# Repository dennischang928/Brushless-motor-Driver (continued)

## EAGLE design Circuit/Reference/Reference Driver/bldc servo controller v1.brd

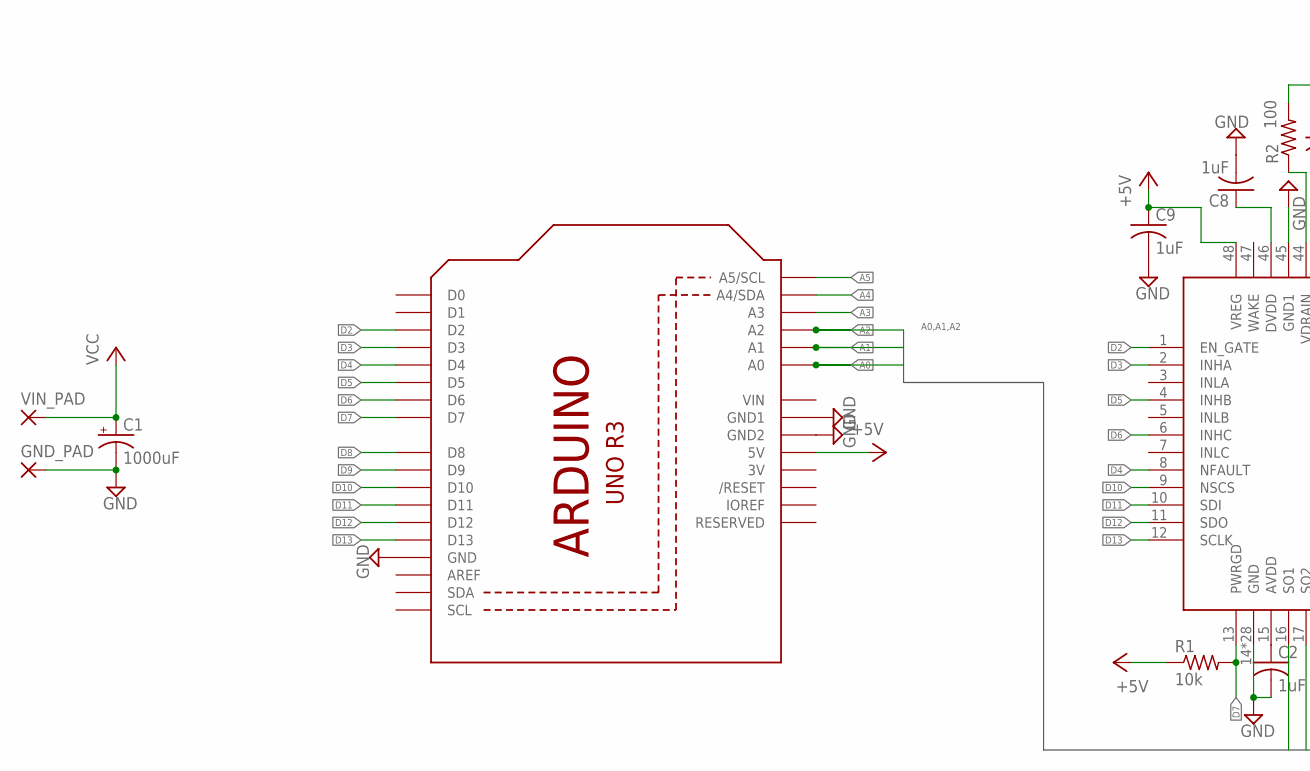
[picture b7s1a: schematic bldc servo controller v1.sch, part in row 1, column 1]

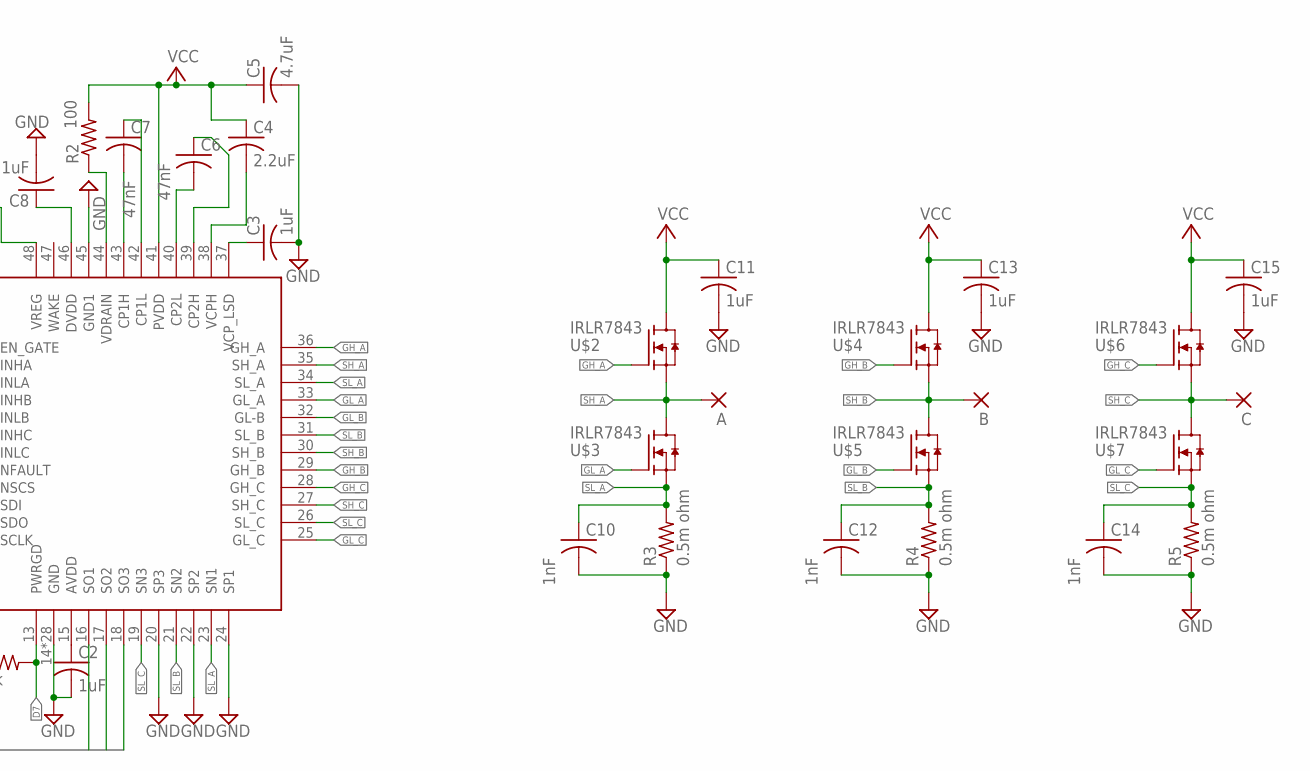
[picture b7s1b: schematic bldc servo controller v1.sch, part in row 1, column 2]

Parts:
A: WIREPAD1,6/0,8; 1,6/0,8
B: WIREPAD1,6/0,8; 1,6/0,8
C: WIREPAD1,6/0,8; 1,6/0,8
C1: 1000uF; E3,5-10
C2, C3, C8, C9, C11, C13, C15: 1uF; C0805
C4: 2.2uF; C0805
C5: 4.7uF; C0805
C6, C7: 47nF; C0805
C10, C12, C14: 1nF; C0805
GND_PAD: WIREPAD1,6/0,8; 1,6/0,8
R1: 10k; M0805
R2: 100; M0805
R3, R4, R5: 0.5m ohm; R2512
U1: ARDUINOR3-BPLACE
U$1: DRV8305; PFB_S-PQFP-G48
U$2, U$3, U$4, U$5, U$6, U$7: IRLR7843; TO252
VIN_PAD: WIREPAD1,6/0,8; 1,6/0,8

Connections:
3V: U1.3V
+5V: C9.1, R1.1, U1.5V, U$1.48 (VREG)
A0: U1.A0, U$1.16 (SO1)
A1: U1.A1, U$1.17 (SO2)
A2: U1.A2, U$1.18 (SO3)
A3: U1.A3
A4: U1.A4 (A4/SDA)
A5: U1.A5 (A5/SCL)
D2: U1.D2, U$1.1 (EN_GATE)
D3: U1.D3, U$1.2 (INHA)
D4: U1.D4, U$1.8 (NFAULT)
D5: U1.D5, U$1.4 (INHB)
D6: U1.D6, U$1.6 (INHC)
D7: R1.2, U1.D7, U$1.13 (PWRGD)
D8: U1.D8
D9: U1.D9
D10: U1.D10, U$1.9 (NSCS)
D11: U1.D11, U$1.10 (SDI)
D12: U1.D12, U$1.11 (SDO)
D13: U1.D13, U$1.12 (SCLK)
GH_A: U$1.36 (GH_A), U$2.1 (G)
GH_B: U$1.29 (GH_B), U$4.1 (G)
GH_C: U$1.28 (GH_C), U$6.1 (G)
GL_A: U$1.33 (GL_A), U$3.1 (G)
GL_B: U$1.32 (GL-B), U$5.1 (G)
GL_C: U$1.25 (GL_C), U$7.1 (G)
GND: C1.-, C2.2, C3.2, C5.2, C8.2, C9.2, C10.2, C11.2, C12.2, C13.2, C14.2, C15.2, GND_PAD.1, R3.1, R4.1, R5.1, U1.GND, U1.GND1, U1.GND2, U$1.14 (GND), U$1.20 (SP3), U$1.22 (SP2), U$1.24 (SP1), U$1.45 (GND1), U$1.P$1 (GND), U$1.P$2 (GND), U$1.P$3 (GND), U$1.P$4 (GND), U$1.P$5 (GND), U$1.P$6 (GND), U$1.P$7 (GND), U$1.P$8 (GND), U$1.P$9 (GND), U$1.P$10 (GND), U$1.P$11 (GND), U$1.P$12 (GND), U$1.P$13 (GND), U$1.P$14 (GND), U$1.P$15 (GND), U$1.P$16 (GND), U$1.P$17 (GND), U$1.P$18 (GND), U$1.P$19 (GND), U$1.P$20 (GND), U$1.P$21 (GND), U$1.P$22 (GND), U$1.P$23 (GND), U$1.P$24 (GND), U$1.P$25 (GND), U$1.P$26 (GND), U$1.P$27 (GND)
unnamed: C2.1, U$1.15 (AVDD)
unnamed: C3.1, U$1.37 (VCP_LSD)
unnamed: C4.2, U$1.38 (VCPH)
unnamed: C6.2, U$1.40 (CP2L)
unnamed: C6.1, U$1.39 (CP2H)
unnamed: C7.2, U$1.43 (CP1H)
unnamed: C7.1, U$1.42 (CP1L)
unnamed: R2.1, U$1.44 (VDRAIN)
unnamed: C8.1, U$1.46 (DVDD)
SH_A: A.1, U$1.35 (SH_A), U$2.2 (S), U$3.3 (D)
SH_B: B.1, U$1.30 (SH_B), U$4.2 (S), U$5.3 (D)
SH_C: C.1, U$1.27 (SH_C), U$6.2 (S), U$7.3 (D)
SL_A: C10.1, R3.2, U$1.23 (SN1), U$1.34 (SL_A), U$3.2 (S)
SL_B: C12.1, R4.2, U$1.21 (SN2), U$1.31 (SL_B), U$5.2 (S)
SL_C: C14.1, R5.2, U$1.19 (SN3), U$1.26 (SL_C), U$7.2 (S)
VCC: C1.+, C4.1, C5.1, C11.1, C13.1, C15.1, R2.2, U$1.41 (PVDD), U$2.3 (D), U$4.3 (D), U$6.3 (D), VIN_PAD.1
VIN: U1.VIN

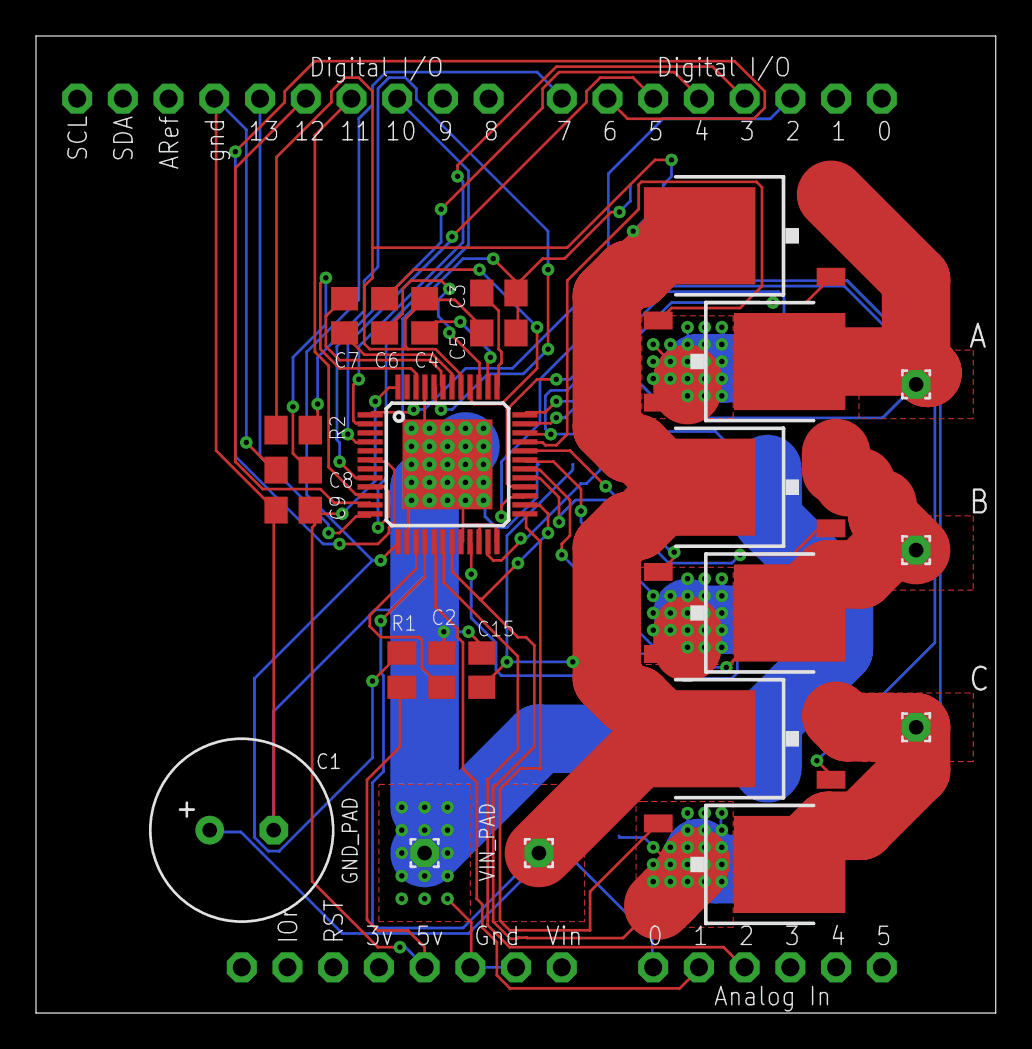
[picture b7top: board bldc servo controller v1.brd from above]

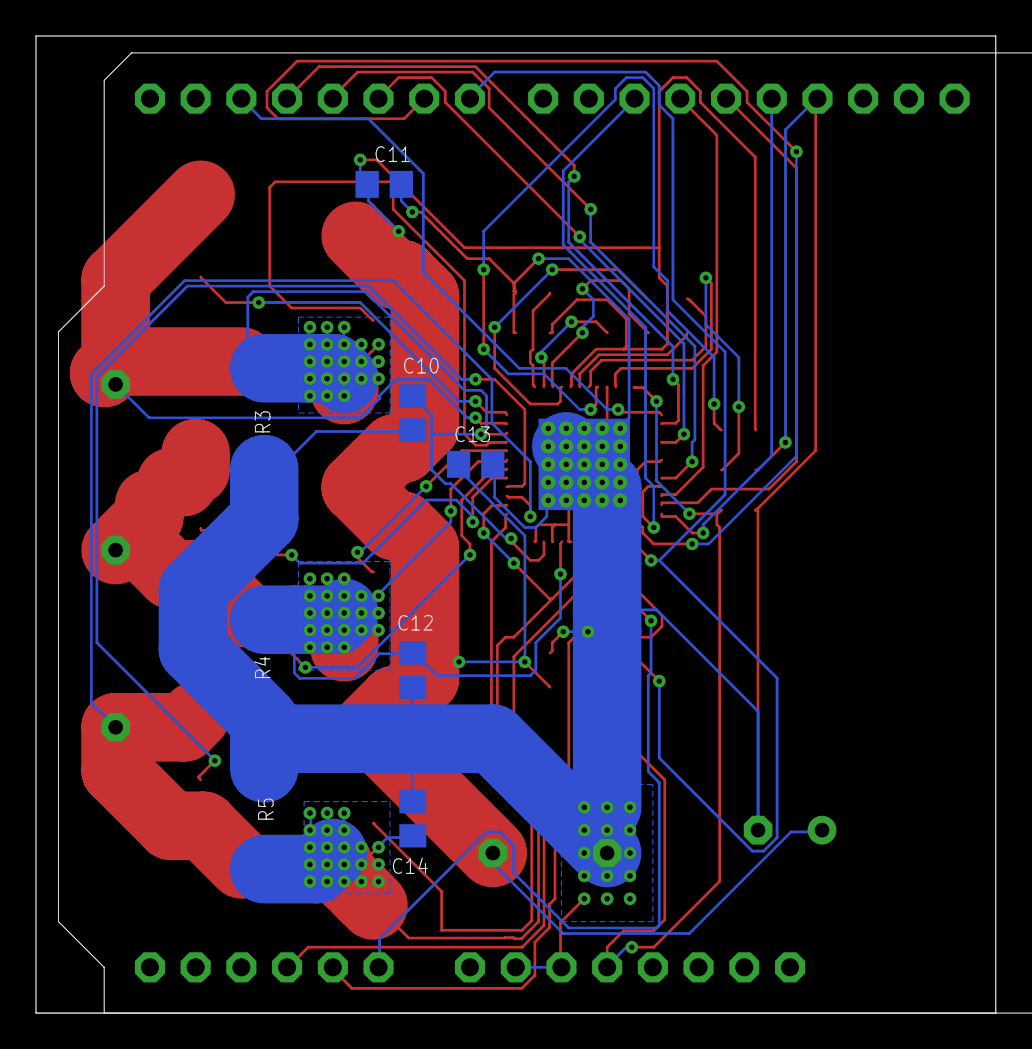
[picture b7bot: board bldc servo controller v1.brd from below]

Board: 2 copper layers, 53.3 x 54.3 mm, 33 parts (8 on the bottom side), 37 nets.

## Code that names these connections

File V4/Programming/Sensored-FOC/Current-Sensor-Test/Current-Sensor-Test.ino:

#include <SimpleFOC.h>
#include <SPI.h>
#include <string>

#define INHA PA8
#define INLA PB6
#define SO1 PA1

#define INHB PA9
#define INLB PB7
#define SO2 PA0

#define INHC PA10
#define INLC PB8

#define NFAULT PB13
#define NOCTW PB14

#define EN_GATE PB12
#define DC_CAL PB4

#define LED PC13

#define chipSelectPin PA4
#define A PA11
#define B PA12
#define Index PA15

#define LED PC13

word data;

BLDCMotor motor = BLDCMotor(7);
BLDCDriver3PWM driver = BLDCDriver3PWM(INHA, INHB, INHC, EN_GATE);

LowsideCurrentSense current_sense = LowsideCurrentSense(1, 20, SO1, SO2, _NC);

HardwareSerial Serial3(PA3, PA2);

void setup()
{
    // VV================MCU and DRV8303 setup================VV
    Serial3.begin(115200);
    pinMode(EN_GATE, OUTPUT);
    pinMode(NFAULT, INPUT);
    pinMode(NOCTW, INPUT);
    pinMode(DC_CAL, OUTPUT);

    digitalWrite(EN_GATE, HIGH);
    digitalWrite(DC_CAL, LOW);

    delay(1);
    SPI_SETUP();
    delay(10);
    changeSPI();
    changeSPIGAIN2_20();
    // ^^================MCU and DRV8303 setup================^^

    driver.voltage_power_supply = 12;
    driver.voltage_limit = 12;
    driver.init();

    current_sense.linkDriver(&driver);

    motor.linkDriver(&driver);

    motor.init();
    current_sense.init();
    motor.linkCurrentSense(&current_sense);

    // motor.initFOC();
    Serial3.println("Motor ready");

    // VV================MCU and DRV8303 setup================VV
    digitalWrite(EN_GATE, HIGH);
    changeSPI();
    _delay(1000);
    // ^^================MCU and DRV8303 setup================^^
}

int Timer = millis();

float i = 1;

void loop()
{
    driver.setPwm(12, 12, 12);
    PhaseCurrent_s currents = current_sense.getPhaseCurrents();

    // Serial3.println(currents.a, 6); // milli Amps
    // Serial3.print("\t");
    Serial3.println(currents.b, 6); // milli Amps
}

float Amplified_Volt2Input_Volt(float Amplified_Volt)
{
    const float K = 2.;
    const float G = 10.;
    const float VREF = 3.3;

    return float((VREF - (K * Amplified_Volt)) / (G * K));
}

float Amplified_Volt2Current(float Amplified_Volt)
{
    const float RRSense = 0.00275256; // 0.5 mOhm
    return float(Amplified_Volt2Input_Volt(Amplified_Volt) / RRSense);
}

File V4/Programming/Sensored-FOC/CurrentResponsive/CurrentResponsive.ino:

#include <SimpleFOC.h>
#include <MovingAverage.h>

#include <SPI.h>

#define INHA PA8
#define INLA PB6
#define SO1 PB1

#define INHB PA9
#define INLB PB7
#define SO2 PB0

#define INHC PA10
#define INLC PB8

#define NFAULT PB13
#define NOCTW PB14

#define EN_GATE PB12
#define DC_CAL PB4

#define LED PC13

#define chipSelectPin PA4
word data;

BLDCMotor motor = BLDCMotor(6);
BLDCDriver3PWM driver = BLDCDriver3PWM(INHA, INHB, INHC, EN_GATE);

HardwareSerial Serial3(PA3, PA2);

MovingAverage CurrentAmpliferA(1);
MovingAverage CurrentAmpliferB(1);

// target variable
float target_velocity = -70;

void changeSPI()
{
  digitalWrite(chipSelectPin, LOW);          // manually take CSN low for SPI_1 transmission
  data = SPI.transfer16(0b0001000000001000); // 0 0010 00000001000
  digitalWrite(chipSelectPin, HIGH);         // manually take CSN high between spi transmissions
}

void changeSPIGAIN2_80()
{
  digitalWrite(chipSelectPin, LOW);          // manually take CSN low for SPI_1 transmission
  data = SPI.transfer16(0b0001100000001100); // 0 0011 00000001000
  digitalWrite(chipSelectPin, HIGH);         // manually take CSN high between spi transmissions
}

void changeSPIGAIN2_40()
{
  digitalWrite(chipSelectPin, LOW);          // manually take CSN low for SPI_1 transmission
  data = SPI.transfer16(0b0001100000001000); // 0 0011 00000001000
  digitalWrite(chipSelectPin, HIGH);         // manually take CSN high between spi transmissions
}

void ReadSPI()
{
  digitalWrite(chipSelectPin, LOW);          // manually take CSN low for SPI_1 transmission
  data = SPI.transfer16(0b1001000000000000); // 1 0010 00000000000
  digitalWrite(chipSelectPin, HIGH);         // manually take CSN high between spi transmissions
}

void ReadStatus()
{
  digitalWrite(chipSelectPin, LOW);          // manually take CSN low for SPI_1 transmission
  data = SPI.transfer16(0b1000000000000000); // 1 0010 00000001000
  digitalWrite(chipSelectPin, HIGH);         // manually take CSN high between spi transmissions
}

void SPI_SETUP()
{
  SPI.begin();
  SPI.setBitOrder(MSBFIRST);
  SPI.setDataMode(SPI_MODE1);
  SPI.setClockDivider(SPI_CLOCK_DIV16);
  pinMode(chipSelectPin, OUTPUT);
}

double offsetA = 0.050946;
double offsetB = 0.050946;
void setup()
{
  Serial3.begin(115200);

  pinMode(INHA, OUTPUT);
  pinMode(INLA, OUTPUT);
  pinMode(SO1, INPUT);

  pinMode(INHB, OUTPUT);
  pinMode(INLB, OUTPUT);
  pinMode(SO2, INPUT);

  pinMode(INHC, OUTPUT);
  pinMode(INLC, OUTPUT);

  pinMode(EN_GATE, OUTPUT);
  pinMode(DC_CAL, OUTPUT);

  pinMode(LED, OUTPUT);
  pinMode(NFAULT, INPUT);
  pinMode(NOCTW, INPUT);

  digitalWrite(DC_CAL, LOW);

  driver.voltage_power_supply = 12;
  driver.voltage_limit = 12;
  driver.init();

  motor.linkDriver(&driver);

  motor.voltage_limit = 12; // [V]

  motor.foc_modulation = FOCModulationType::SpaceVectorPWM;
  motor.controller = MotionControlType::velocity_openloop;

  // init motor hardware
  motor.init();

  SPI_SETUP();
  changeSPIGAIN2_40();
  delay(1000);
  changeSPI();
}

int Timer = millis();

float i = 1;

void loop()
{
  Serial3.print(analogRead(SO1) / 1023. * 3.3 * 1000);
  Serial3.print('\t');
  Serial3.println(analogRead(SO2) / 1023. * 3.3 * 1000);
}

double GetShuntResistorVoltage(double RawVolt)
{
  const double G = 40.;
  const double VREF = 3.3;
  return ((VREF / 2.) - RawVolt) / G; // general solve
}

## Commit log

2021-10-14 Create Folder and Notes, and add some prepare works for Circuit (Add a 'Blue Pill')
2021-10-15 Add the mosfets and their driver to the BLDC Driver sch
2021-10-17 Finish drawing the PCB for 1 stage(not add external layer yet, not autoroutering yet)
2021-10-19 before adding pinhead
2021-10-21 enlarged the width of the vin and added a T-stop wire for large current signal (mosfet GND and VCC)
2021-10-21 add a 5V pad input, delete the connection of Vin and Vbat, and add Description in Tname
2021-10-21 fixed some bugs(Erc and Drc Errors)
2021-10-21 Fixed the PVDD and VDrain pin's 'Vin' problem, Fixed some bugs
2021-10-21 Add polygon Ratsnest
2021-10-21 Adding CAM Output Files for V1. Delete some Eagle build-in History files
2021-10-27 2MCU CAN commiucation tested
2021-10-30 Added a BLDC_Driver_Testing folder for testing DRV8053
2021-10-30 Added multiple MCU commuication test folder
2021-10-30 Folder rearrange
2021-11-04 tested DRV8305's pin AH BL enable. But not working because of the overcurrent protecting
2021-11-07 Trying to change the config of DRV8305, but seems that the overcurrent problem doesn't go well
2021-11-07 Added a PDF about my V1 Testing circuit.
2021-11-07 Added NSS pin
2021-11-08 Finally found the solution (The problem isn't about overcurrent. The PVDD_UVLO2 fault is the one.) (Tried to disable the PVDD_UVLO2 setting, but because of the current limitation of Power Supply, The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
2021-11-09 After Changing the PVDD_UVLO2 config, I manually input the sequence of the BLDC motor rotations, success fully rotate the BLDC, but there are some vibration.
2021-11-13 Successfully rotate the BLDC
    Successfully rotate the BLDC using FOC (*only work in 3 PWM mode*). Fix the library bug by changing the C++ file of the Simple FOC library in the Library_Specify folder.
2021-12-30 Code-Update
    Update
2021-12-30 Preparation of the V2 Driver Circuit board
2021-12-31 Designed and auto routed BLDC driver V2 circuit
2021-12-31 Deleted all the autorouting signal
2021-12-31 Manually routed the Shunt resistor detection signal to the Gate driver
2021-12-31 Fix some routering bug
2021-12-31 Mirror the PCB arrangement
2022-01-08 Generated the CAM file of the V2 board
2022-01-08 organized the BLDC testing files
2022-01-10 Tidy up the code and prepared for V3 circuit board
2022-01-10 Added a file inside the Library_Specify directory
2022-01-13 Change the orginal motor gate driver(DRV8305) to DRV8303 in schematic
2022-01-13 Routing the basic circuit and route. A backup before autorouting
2022-01-14 Fixed some bugs and edited the note.md
2022-01-14 Fixed some bugs
2022-01-14 autorouted the circuit
2022-01-29 Preparation for DRV8303
2022-01-29 Tested out the new Driver
2022-03-05 New Version-Preparation
2022-03-05 Initalization of V1.1
2022-03-05 Circuit preparation (Added stm32 and DRV8300)
2022-03-11 Circuit: Added DRV8300, and the Gate Circuit. Haven't added the Not gate
2022-03-11 Added the FOC library
2022-03-12 Added Not Gate to the circuit
2022-03-16 Ready for autoroutering
2022-03-16 Ready for autoroutering 2
2022-03-16 Ready for autoroutering 3
2022-03-16 Ready for autoroutering 4
2022-03-16 Ready for autoroutering 5
2022-03-17 Ready for autoroutering 6
2022-04-02 Prepare for circuit
2022-04-02 Prepared for V2
2022-04-02 Designed V2, Ready for autoroutering 1
2022-04-02 Designed V2, Ready for autoroutering 2
2022-04-27 Generated the Gerber files of the circuit
2022-07-16 Ready for V3-DRV8303
2022-07-16 Prepared for V3-DRV8300 PCB routing
2022-07-16 Prepared for V3-DRV8300 PCB routing 3
2022-07-16 V3-DRV8303 PCB Routed
2022-07-17 Removed the signal than blocks the AGND to the powerpad; Ready for autorouting
2022-07-17 Moving two vias, the AGND signal have a better conductivity to the power pad
2022-07-17 Generated the V3.1 DRV8303 Gerber files
2022-08-22 Prepare for DRV8303 Tester board
2022-08-23 Ready for autoroutering (Tester)
2022-08-23 Ready for autoroutering (Tester) 2
2022-08-23 Ready for autoroutering (Tester) 3
2022-08-23 Ready for autoroutering (Tester) 4
2022-08-23 Ready for autoroutering (Tester) 5
2022-08-23 Ready for autoroutering (Tester) 6
2022-08-23 Ready for autoroutering (Tester) 7
2022-08-23 Autoroutered the tester board
2022-08-23 Generated Gerber file
2022-08-23 Generated Gerber file v2 (with via masked)
2022-08-23 Generated Gerber file v3 (deleted bottom polygon signal)
2022-10-06 Added 2 Current Test (Current Amplifier responsive test and Current Amplifier output to input)
2022-10-08 Successfully measure the current using the SimpleFOC library
2022-10-08 Changed all the PWM output pin to the same timer, Added 2 selector for C.S.A.
2022-10-08 Ready for auto routering 2
2022-10-08 Routed all signal, ready for gerber gen
2022-10-08 Fixed a little mistake/bug (PA2 -> PA0)
2022-10-14 Update the Note.md file, changed the PWM pins notes
2022-10-22 Prepared for Magnetic Encoder test using simple foc library
2022-10-25 之前嘅Current sense問題已經搵到 而家用緊一個encoder 嚟做 voltage torque close loop control MotionControlType::torque
2022-12-15 Prepared for V4 design
2022-12-21 Ready for V4 autoroutering
2022-12-21 Ready for V4 autoroutering 3
2022-12-21 Ready for V4 autoroutering 4
2022-12-21 Ready for V4 autoroutering 5
2022-12-21 Ready for V4 autoroutering 7
2022-12-21 Ready for V4 autoroutering 8
2022-12-21 Finished autoRouter
2022-12-22 Exported V4 circuit
2022-12-22 Exported a new version V4 circuit [Changes: Added a new ratsnest]
2023-01-19 Velocity Closed Loop successed (with sensorless FOC and without proper PID tuning) Motor gets stuck when Target velocity rises above 90
2023-01-19 Testing DRV8303 current amplifier
2023-01-19 Failed to use Simple FOC's lowsidecurrent sense to sense current
2023-01-31 Current Responsive test successed
2023-02-01 Successed! Found that the problem is about the value of Gain, change Gain: 10 -> 80 because 0.05mohm is too small with 10V gain, the noise overlapped the amplified signal
2023-02-10 Tuned Uq Ud pid in The folder{CurrentSensored-Torque-Control} (Not perfect but works somehow)
2023-03-06 Added a README file
